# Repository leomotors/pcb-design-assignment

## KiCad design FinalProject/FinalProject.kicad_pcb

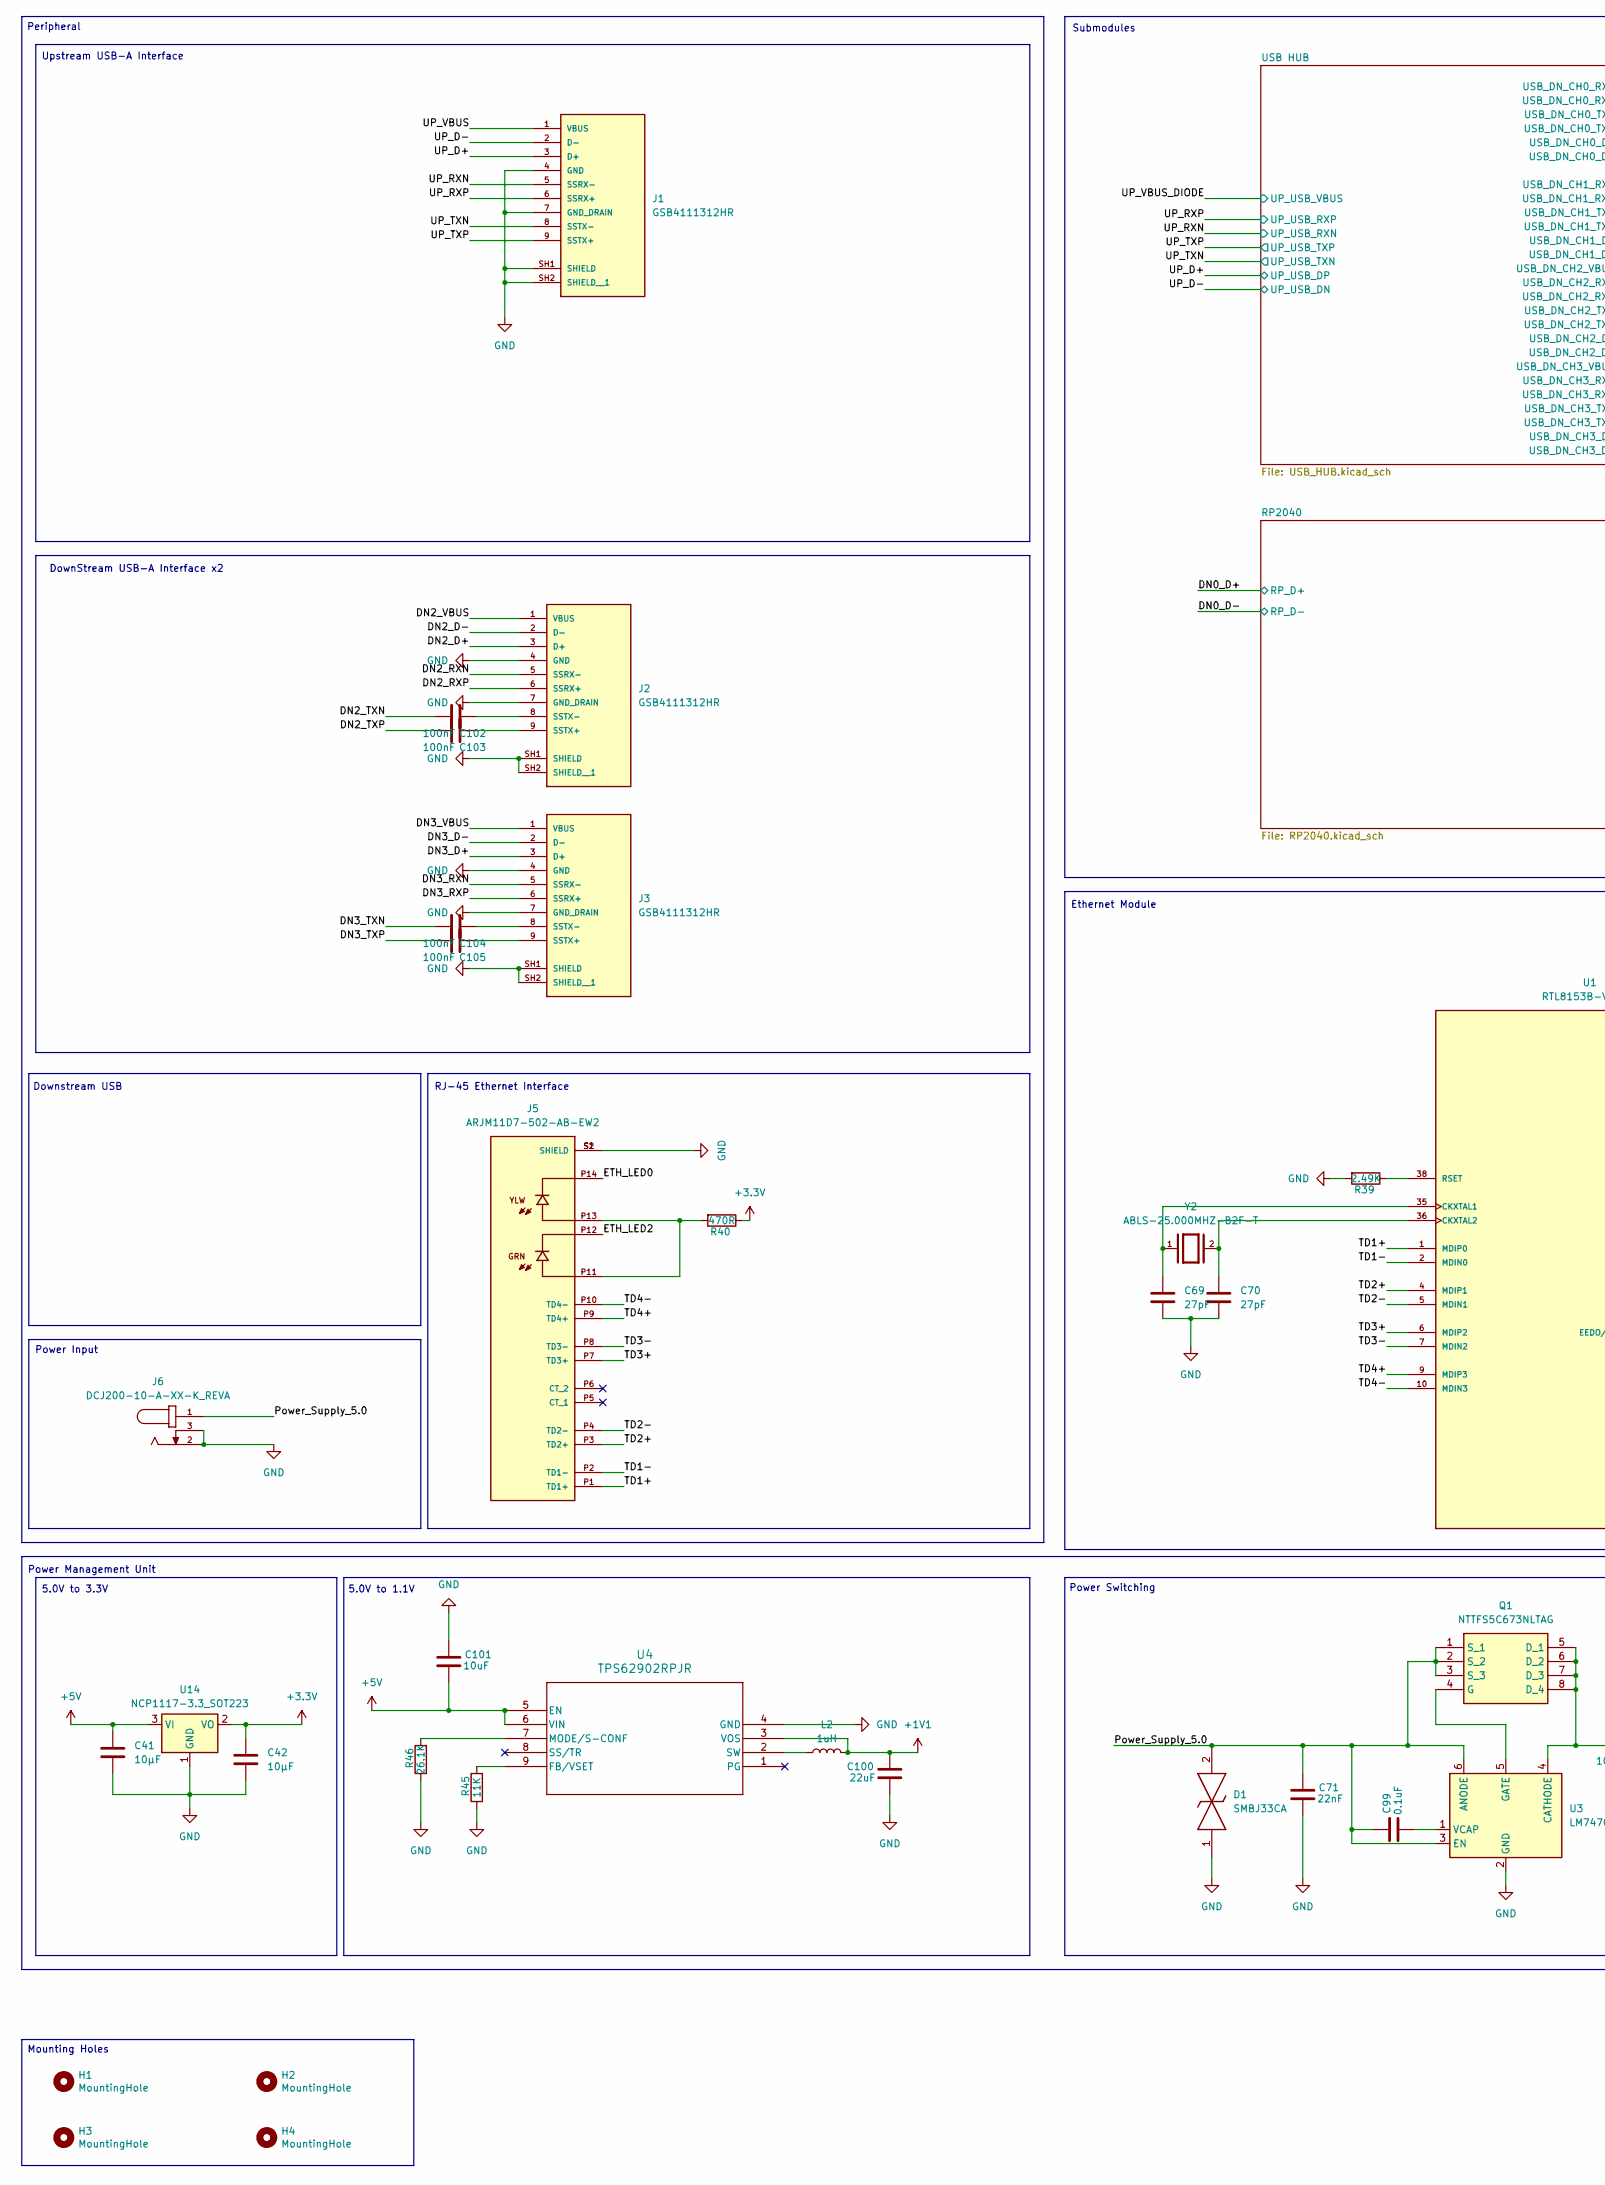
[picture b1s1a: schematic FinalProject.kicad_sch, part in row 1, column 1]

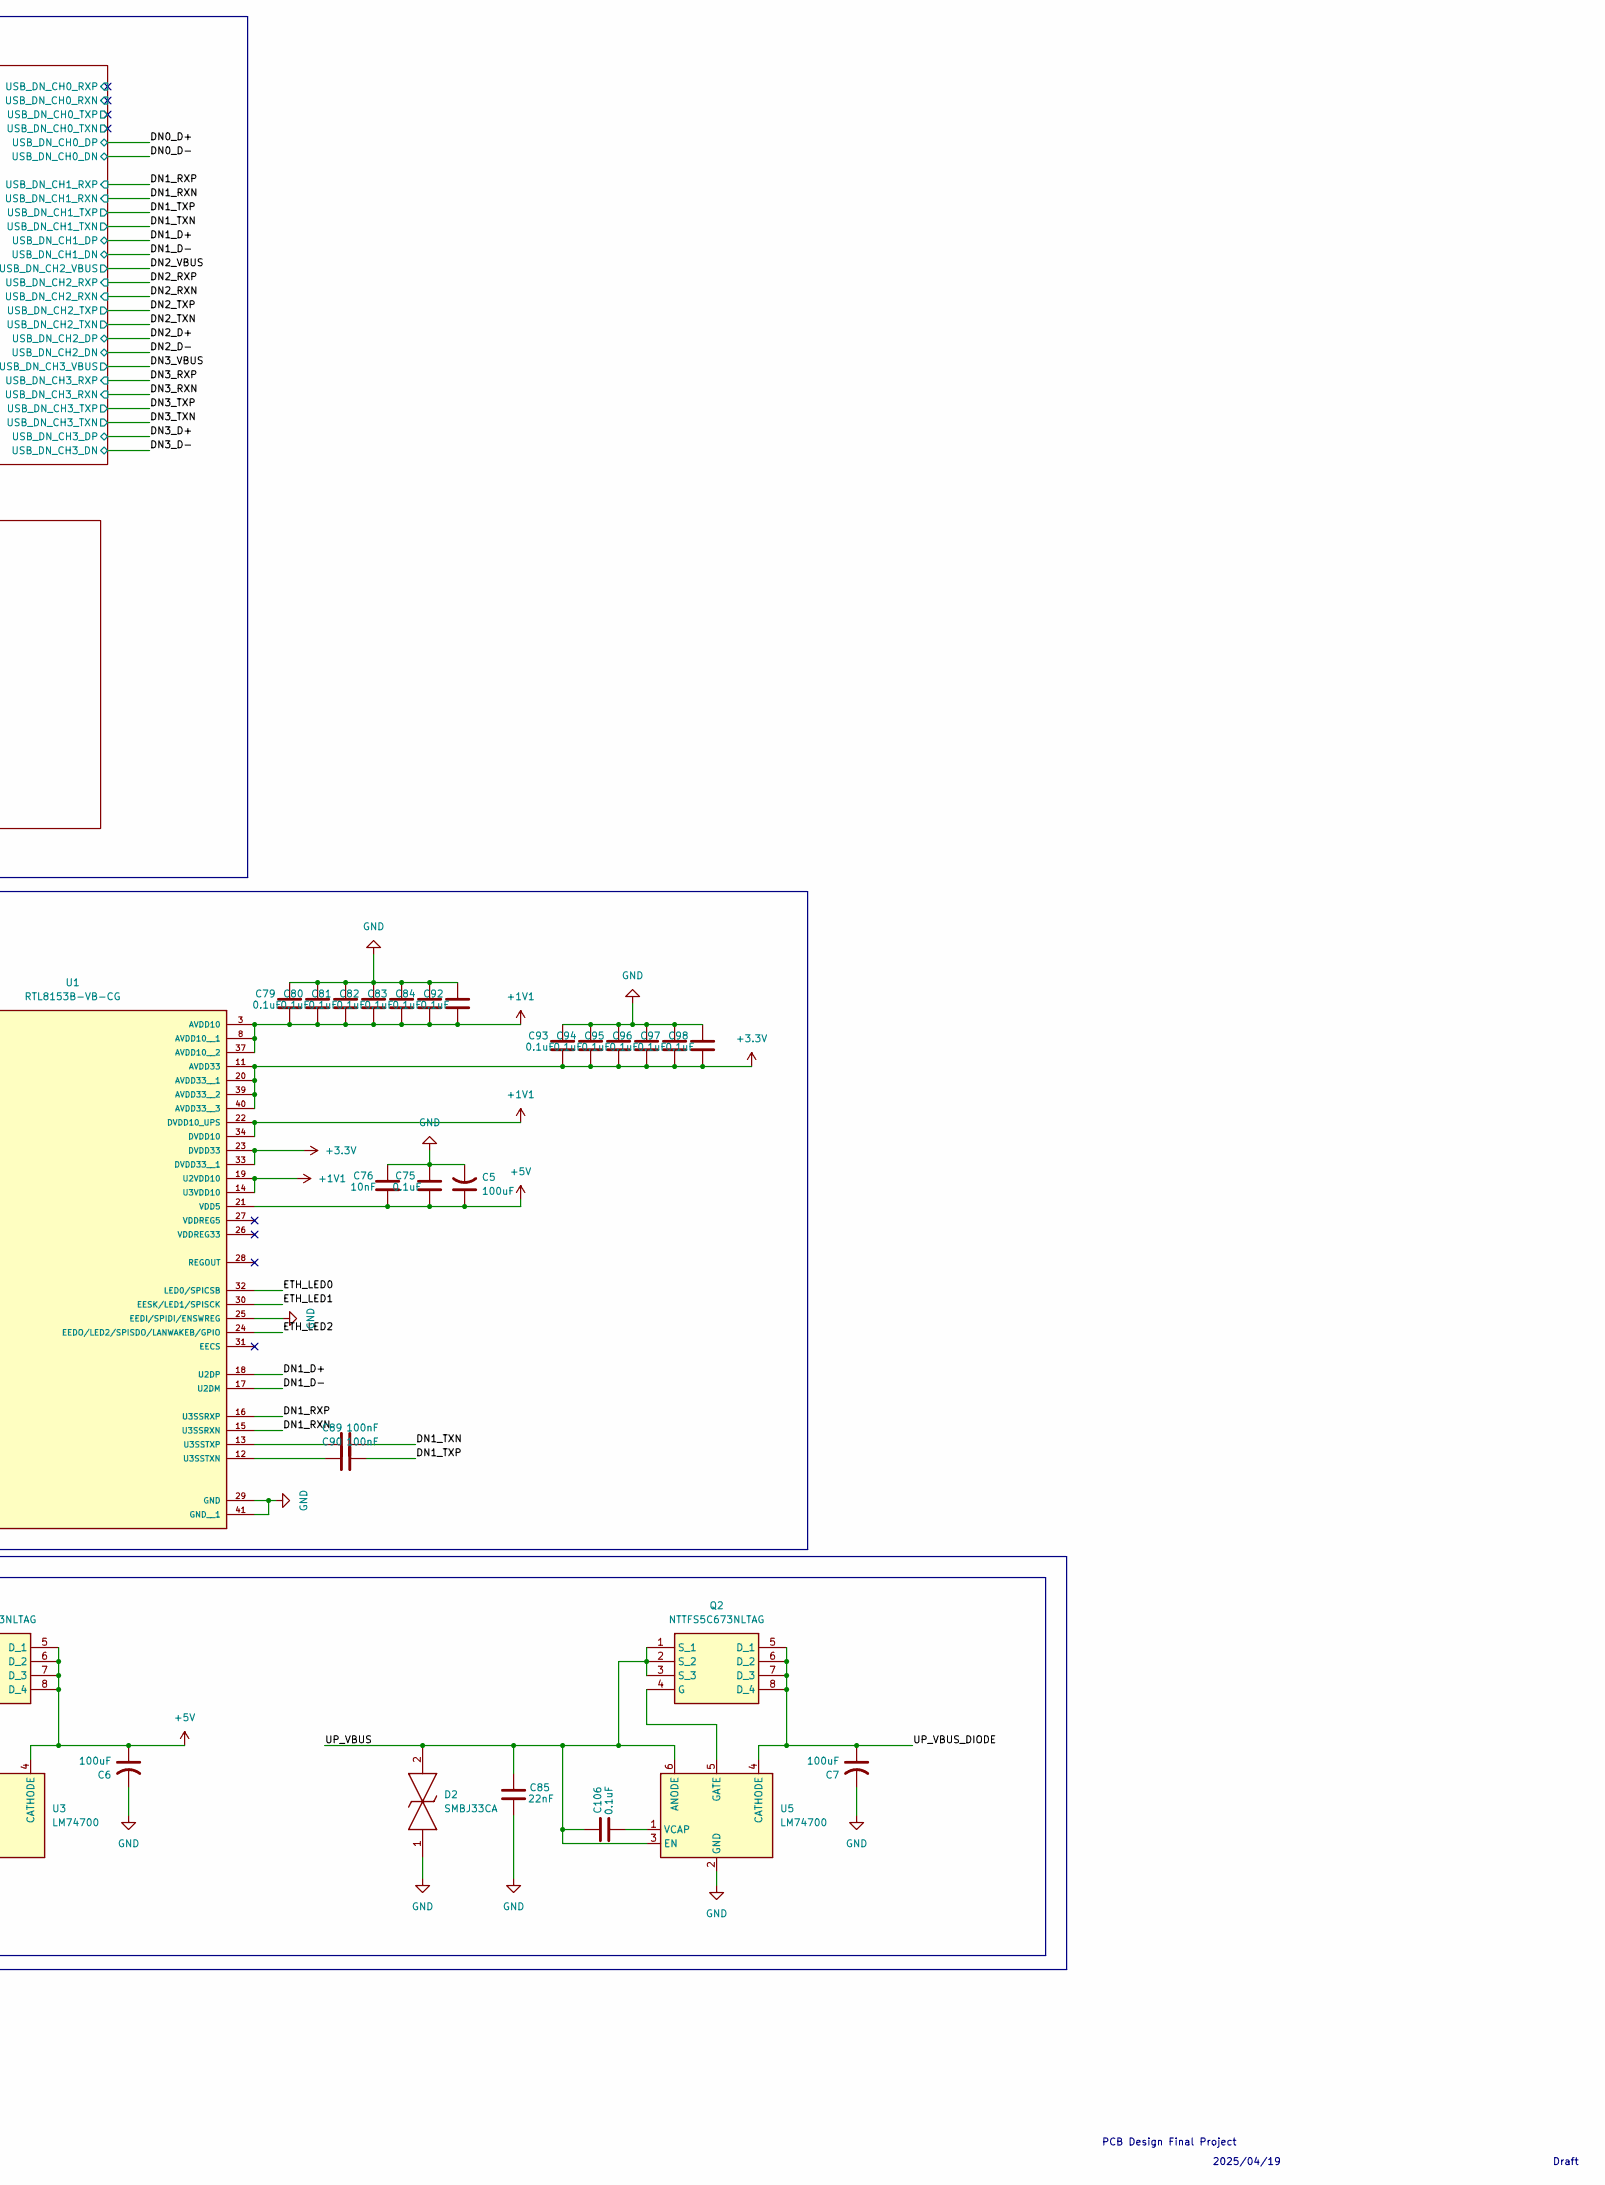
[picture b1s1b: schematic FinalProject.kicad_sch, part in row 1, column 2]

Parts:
C5, C6, C7: 100uF; C_1206_3216Metric
C41, C42: 10μF; C_0603_1608Metric
C69, C70: 27pF; C_0603_1608Metric
C71, C85: 22nF; C_0603_1608Metric
C75, C79, C80, C81, C82, C83, C84, C92, C93, C94, C95, C96, C97, C98, C99, C106: 0.1uF; C_0603_1608Metric
C76: 10nF; C_0603_1608Metric
C89, C90, C102, C103, C104, C105: 100nF; C_0603_1608Metric
C100: 22uF; C_0603_1608Metric
C101: 10uF; C_0603_1608Metric
D1, D2: SMBJ33CA; DIONM5436X261N; Mouser Part Number 576-SMBJ33CA
H1, H2, H3, H4: MountingHole; MountingHole_2.7mm_M2.5
J1, J2, J3: GSB4111312HR; AMPHENOL_GSB4111312HR; PARTREV B
J5: ARJM11D7-502-AB-EW2; ABRACON_ARJM11D7-502-AB-EW2; PARTREV 01-21-20
J6: DCJ200-10-A-XX-K_REVA; GCT_DCJ200-10-A-XX-K_REVA; PARTREV A
L2: 1uH; L_1008_2520Metric
Q1, Q2: NTTFS5C673NLTAG; NVTFS6H854NTAG; Mouser Part Number 863-NTTFS5C673NLTAG
R39: 2.49K; R_0603_1608Metric
R40: 470R; R_0603_1608Metric
R45: 11K; R_0603_1608Metric
R46: 26.1K; R_0603_1608Metric
U1: RTL8153B-VB-CG; QFN40P500X500X90-41N; PARTREV 1.4
U3, U5: LM74700; SOT-23-6
U4: TPS62902RPJR; QFN_902RPJR_TEX
U14: NCP1117-3.3_SOT223; SOT-223-3_TabPin2
Y2: ABLS-25.000MHZ-B2F-T; XTAL_ABLS-25.000MHZ-B2F-T; PARTREV 02.16.2021

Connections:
+1V1: C79.2, C80.2, C81.2, C82.2, C83.2, C84.2, C92.2, C100.1, L2.2, U1.3 (AVDD10), U1.8 (AVDD10__1), U1.14 (U3VDD10), U1.19 (U2VDD10), U1.22 (DVDD10_UPS), U1.34 (DVDD10), U1.37 (AVDD10__2), U4.3 (VOS); also elsewhere on the board
+3.3V: C42.1, C93.2, C94.2, C95.2, C96.2, C97.2, C98.2, R40.1, U1.11 (AVDD33), U1.20 (AVDD33__1), U1.23 (DVDD33), U1.33 (DVDD33__1), U1.39 (AVDD33__2), U1.40 (AVDD33__3), U14.2 (VO); also elsewhere on the board
+5V: C5.1, C6.1, C41.1, C75.2, C76.2, C101.2, Q1.5 (D_1), Q1.6 (D_2), Q1.7 (D_3), Q1.8 (D_4), U1.21 (VDD5), U3.4 (CATHODE), U4.5 (EN), U4.6 (VIN), U14.3 (VI); also elsewhere on the board
/DN1_D+: U1.18 (U2DP); also elsewhere on the board
/DN1_D-: U1.17 (U2DM); also elsewhere on the board
/DN1_RXN: U1.15 (U3SSRXN); also elsewhere on the board
/DN1_RXP: U1.16 (U3SSRXP); also elsewhere on the board
/DN1_TXN: C89.2; also elsewhere on the board
/DN1_TXP: C90.2; also elsewhere on the board
/DN2_D+: J2.3 (D+); also elsewhere on the board
/DN2_D-: J2.2 (D-); also elsewhere on the board
/DN2_RXN: J2.5 (SSRX-); also elsewhere on the board
/DN2_RXP: J2.6 (SSRX+); also elsewhere on the board
/DN2_TXN: C102.2; also elsewhere on the board
/DN2_TXP: C103.2; also elsewhere on the board
/DN2_VBUS: J2.1 (VBUS); also elsewhere on the board
/DN3_D+: J3.3 (D+); also elsewhere on the board
/DN3_D-: J3.2 (D-); also elsewhere on the board
/DN3_RXN: J3.5 (SSRX-); also elsewhere on the board
/DN3_RXP: J3.6 (SSRX+); also elsewhere on the board
/DN3_TXN: C104.2; also elsewhere on the board
/DN3_TXP: C105.2; also elsewhere on the board
/DN3_VBUS: J3.1 (VBUS); also elsewhere on the board
/ETH_LED0: J5.P14, U1.32 (LED0/SPICSB)
/ETH_LED1: U1.30 (EESK/LED1/SPISCK)
/ETH_LED2: J5.P12, U1.24 (EEDO/LED2/SPISDO/LANWAKEB/GPIO)
/Power_Supply_5.0: C71.1, C99.1, D1.2, J6.1, Q1.1 (S_1), Q1.2 (S_2), Q1.3 (S_3), U3.3 (EN), U3.6 (ANODE)
/TD1+: J5.P1 (TD1+), U1.1 (MDIP0)
/TD1-: J5.P2 (TD1-), U1.2 (MDIN0)
/TD2+: J5.P3 (TD2+), U1.4 (MDIP1)
/TD2-: J5.P4 (TD2-), U1.5 (MDIN1)
/TD3+: J5.P7 (TD3+), U1.6 (MDIP2)
/TD3-: J5.P8 (TD3-), U1.7 (MDIN2)
/TD4+: J5.P9 (TD4+), U1.9 (MDIP3)
/TD4-: J5.P10 (TD4-), U1.10 (MDIN3)
/UP_D+: J1.3 (D+); also elsewhere on the board
/UP_D-: J1.2 (D-); also elsewhere on the board
/UP_RXN: J1.5 (SSRX-); also elsewhere on the board
/UP_RXP: J1.6 (SSRX+); also elsewhere on the board
/UP_TXN: J1.8 (SSTX-); also elsewhere on the board
/UP_TXP: J1.9 (SSTX+); also elsewhere on the board
/UP_VBUS: C85.1, C106.1, D2.2, J1.1 (VBUS), Q2.1 (S_1), Q2.2 (S_2), Q2.3 (S_3), U5.3 (EN), U5.6 (ANODE)
/UP_VBUS_DIODE: C7.1, Q2.5 (D_1), Q2.6 (D_2), Q2.7 (D_3), Q2.8 (D_4), U5.4 (CATHODE); also elsewhere on the board
GND: C5.2, C6.2, C7.2, C41.2, C42.2, C69.2, C70.2, C71.2, C75.1, C76.1, C79.1, C80.1, C81.1, C82.1, C83.1, C84.1, C85.2, C92.1, C93.1, C94.1, C95.1, C96.1, C97.1, C98.1, C100.2, C101.1, D1.1, D2.1, J1.4 (GND), J1.7 (GND_DRAIN), J1.SH1 (SHIELD), J1.SH2 (SHIELD__1), J2.4 (GND), J2.7 (GND_DRAIN), J2.SH1 (SHIELD), J2.SH2 (SHIELD__1), J3.4 (GND), J3.7 (GND_DRAIN), J3.SH1 (SHIELD), J3.SH2 (SHIELD__1), J5.S1 (SHIELD), J5.S2 (SHIELD), J6.2, J6.3, R39.2, R45.1, R46.1, U1.25 (EEDI/SPIDI/ENSWREG), U1.29 (GND), U1.41 (GND__1), U3.2 (GND), U4.4 (GND), U5.2 (GND), U14.1 (GND); also elsewhere on the board
unnamed: C103.1, J2.9 (SSTX+)
unnamed: C102.1, J2.8 (SSTX-)
unnamed: C105.1, J3.9 (SSTX+)
unnamed: C104.1, J3.8 (SSTX-)
unnamed: J5.P11, J5.P13, R40.2
unnamed: Q1.4 (G), U3.5 (GATE)
unnamed: Q2.4 (G), U5.5 (GATE)
unnamed: C69.1, U1.35 (CKXTAL1), Y2.1
unnamed: C70.1, U1.36 (CKXTAL2), Y2.2
unnamed: R39.1, U1.38 (RSET)
unnamed: C90.1, U1.12 (U3SSTXN)
unnamed: C89.1, U1.13 (U3SSTXP)
unnamed: C99.2, U3.1 (VCAP)
unnamed: R45.2, U4.9 (FB/VSET)
unnamed: R46.2, U4.7 (MODE/S-CONF)
unnamed: L2.1, U4.2 (SW)
unnamed: C106.2, U5.1 (VCAP)

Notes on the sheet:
Downstream USB
2025/04/19
RJ-45 Ethernet Interface
Draft
PCB Design Final Project
5.0V to 1.1V
Ethernet Module
DownStream USB-A Interface x2
5.0V to 3.3V
Upstream USB-A Interface
Submodules
Power Switching
Power Management Unit
Peripheral
Power Input
Mounting Holes

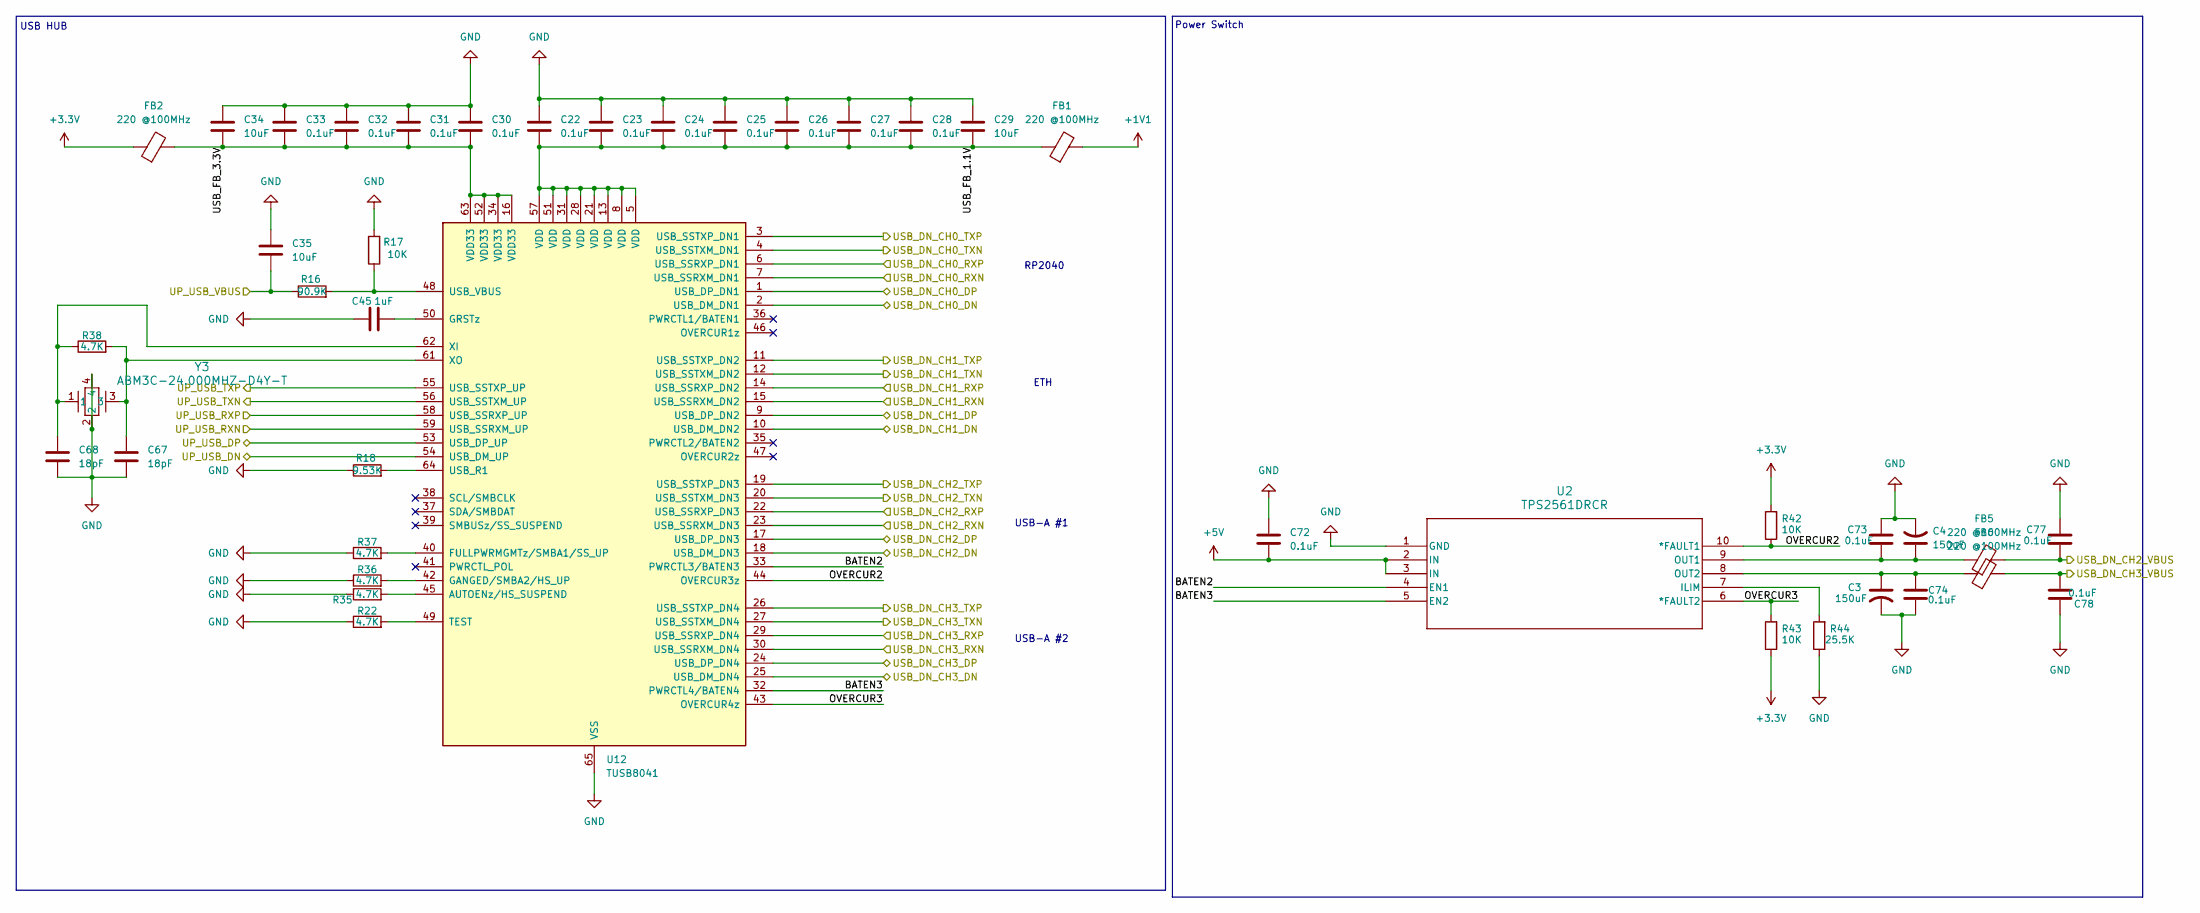
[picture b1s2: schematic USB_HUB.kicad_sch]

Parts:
C3, C4: 150uF; C_1210_3225Metric
C22, C23, C24, C25, C26, C27, C28, C30, C31, C32, C33, C72, C73, C74, C77, C78: 0.1uF; C_0603_1608Metric
C29, C34, C35: 10uF; C_0603_1608Metric
C45: 1uF; C_0603_1608Metric
C67, C68: 18pF; C_0603_1608Metric
FB1, FB2, FB5, FB6: 220 @100MHz; L_0805_2012Metric
R16: 90.9K; R_0402_1005Metric
R17, R42, R43: 10K; R_0402_1005Metric
R18: 9.53K; R_0402_1005Metric
R22, R38: 4.7K; R_0603_1608Metric
R35, R36, R37: 4.7K; R_0402_1005Metric
R44: 25.5K; R_0402_1005Metric
U2: TPS2561DRCR; DRC10_2P4X1P65
U12: TUSB8041; QFN-64-1EP_9x9mm_P0.5mm_EP6x6mm_ThermalVias
Y3: ABM3C-24.000MHZ-D4Y-T; CRYSTAL_ABM3C_ABR

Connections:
+1V1: FB1.2; also elsewhere on the board
+3.3V: FB2.1, R42.2, R43.1; also elsewhere on the board
+5V: C72.2, U2.2 (IN), U2.3 (IN); also elsewhere on the board
/DN0_D+: U12.1 (USB_DP_DN1); also elsewhere on the board
/DN0_D-: U12.2 (USB_DM_DN1); also elsewhere on the board
/DN1_D+: U12.9 (USB_DP_DN2); also elsewhere on the board
/DN1_D-: U12.10 (USB_DM_DN2); also elsewhere on the board
/DN1_RXN: U12.15 (USB_SSRXM_DN2); also elsewhere on the board
/DN1_RXP: U12.14 (USB_SSRXP_DN2); also elsewhere on the board
/DN1_TXN: U12.12 (USB_SSTXM_DN2); also elsewhere on the board
/DN1_TXP: U12.11 (USB_SSTXP_DN2); also elsewhere on the board
/DN2_D+: U12.17 (USB_DP_DN3); also elsewhere on the board
/DN2_D-: U12.18 (USB_DM_DN3); also elsewhere on the board
/DN2_RXN: U12.23 (USB_SSRXM_DN3); also elsewhere on the board
/DN2_RXP: U12.22 (USB_SSRXP_DN3); also elsewhere on the board
/DN2_TXN: U12.20 (USB_SSTXM_DN3); also elsewhere on the board
/DN2_TXP: U12.19 (USB_SSTXP_DN3); also elsewhere on the board
/DN2_VBUS: C77.2, FB5.2; also elsewhere on the board
/DN3_D+: U12.24 (USB_DP_DN4); also elsewhere on the board
/DN3_D-: U12.25 (USB_DM_DN4); also elsewhere on the board
/DN3_RXN: U12.30 (USB_SSRXM_DN4); also elsewhere on the board
/DN3_RXP: U12.29 (USB_SSRXP_DN4); also elsewhere on the board
/DN3_TXN: U12.27 (USB_SSTXM_DN4); also elsewhere on the board
/DN3_TXP: U12.26 (USB_SSTXP_DN4); also elsewhere on the board
/DN3_VBUS: C78.2, FB6.2; also elsewhere on the board
/UP_D+: U12.53 (USB_DP_UP); also elsewhere on the board
/UP_D-: U12.54 (USB_DM_UP); also elsewhere on the board
/UP_RXN: U12.59 (USB_SSRXM_UP); also elsewhere on the board
/UP_RXP: U12.58 (USB_SSRXP_UP); also elsewhere on the board
/UP_TXN: U12.56 (USB_SSTXM_UP); also elsewhere on the board
/UP_TXP: U12.55 (USB_SSTXP_UP); also elsewhere on the board
/UP_VBUS_DIODE: C35.2, R16.1; also elsewhere on the board
/USB HUB/BATEN2: U2.4 (EN1), U12.33 (PWRCTL3/BATEN3)
/USB HUB/BATEN3: U2.5 (EN2), U12.32 (PWRCTL4/BATEN4)
/USB HUB/OVERCUR2: R42.1, U2.10 (*FAULT1), U12.44 (OVERCUR3z)
/USB HUB/OVERCUR3: R43.2, U2.6 (*FAULT2), U12.43 (OVERCUR4z)
/USB HUB/USB_DN_CH0_RXN: U12.7 (USB_SSRXM_DN1)
/USB HUB/USB_DN_CH0_RXP: U12.6 (USB_SSRXP_DN1)
/USB HUB/USB_DN_CH0_TXN: U12.4 (USB_SSTXM_DN1)
/USB HUB/USB_DN_CH0_TXP: U12.3 (USB_SSTXP_DN1)
/USB HUB/USB_FB_1.1V: C22.2, C23.2, C24.2, C25.2, C26.2, C27.2, C28.2, C29.2, FB1.1, U12.5 (VDD), U12.8 (VDD), U12.13 (VDD), U12.21 (VDD), U12.28 (VDD), U12.31 (VDD), U12.51 (VDD), U12.57 (VDD)
/USB HUB/USB_FB_3.3V: C30.2, C31.2, C32.2, C33.2, C34.2, FB2.2, U12.16 (VDD33), U12.34 (VDD33), U12.52 (VDD33), U12.63 (VDD33)
GND: C3.2, C4.2, C22.1, C23.1, C24.1, C25.1, C26.1, C27.1, C28.1, C29.1, C30.1, C31.1, C32.1, C33.1, C34.1, C35.1, C45.1, C67.2, C68.2, C72.1, C73.1, C74.1, C77.1, C78.1, R17.2, R18.1, R22.1, R35.1, R36.1, R37.1, R44.1, U2.1 (GND), U12.65 (VSS), Y3.2, Y3.4; also elsewhere on the board
unnamed: R44.2, U2.7 (ILIM)
unnamed: C4.1, C73.2, FB5.1, U2.9 (OUT1)
unnamed: C3.1, C74.2, FB6.1, U2.8 (OUT2)
unnamed: R35.2, U12.45 (AUTOENz/HS_SUSPEND)
unnamed: R37.2, U12.40 (FULLPWRMGMTz/SMBA1/SS_UP)
unnamed: R36.2, U12.42 (GANGED/SMBA2/HS_UP)
unnamed: C45.2, U12.50 (GRSTz)
unnamed: R22.2, U12.49 (TEST)
unnamed: R18.2, U12.64 (USB_R1)
unnamed: R16.2, R17.1, U12.48 (USB_VBUS)
unnamed: C68.1, R38.1, U12.62 (XI), Y3.1
unnamed: C67.1, R38.2, U12.61 (XO), Y3.3

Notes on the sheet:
USB HUB
USB-A #1
RP2040
USB-A #2
ETH
Power Switch

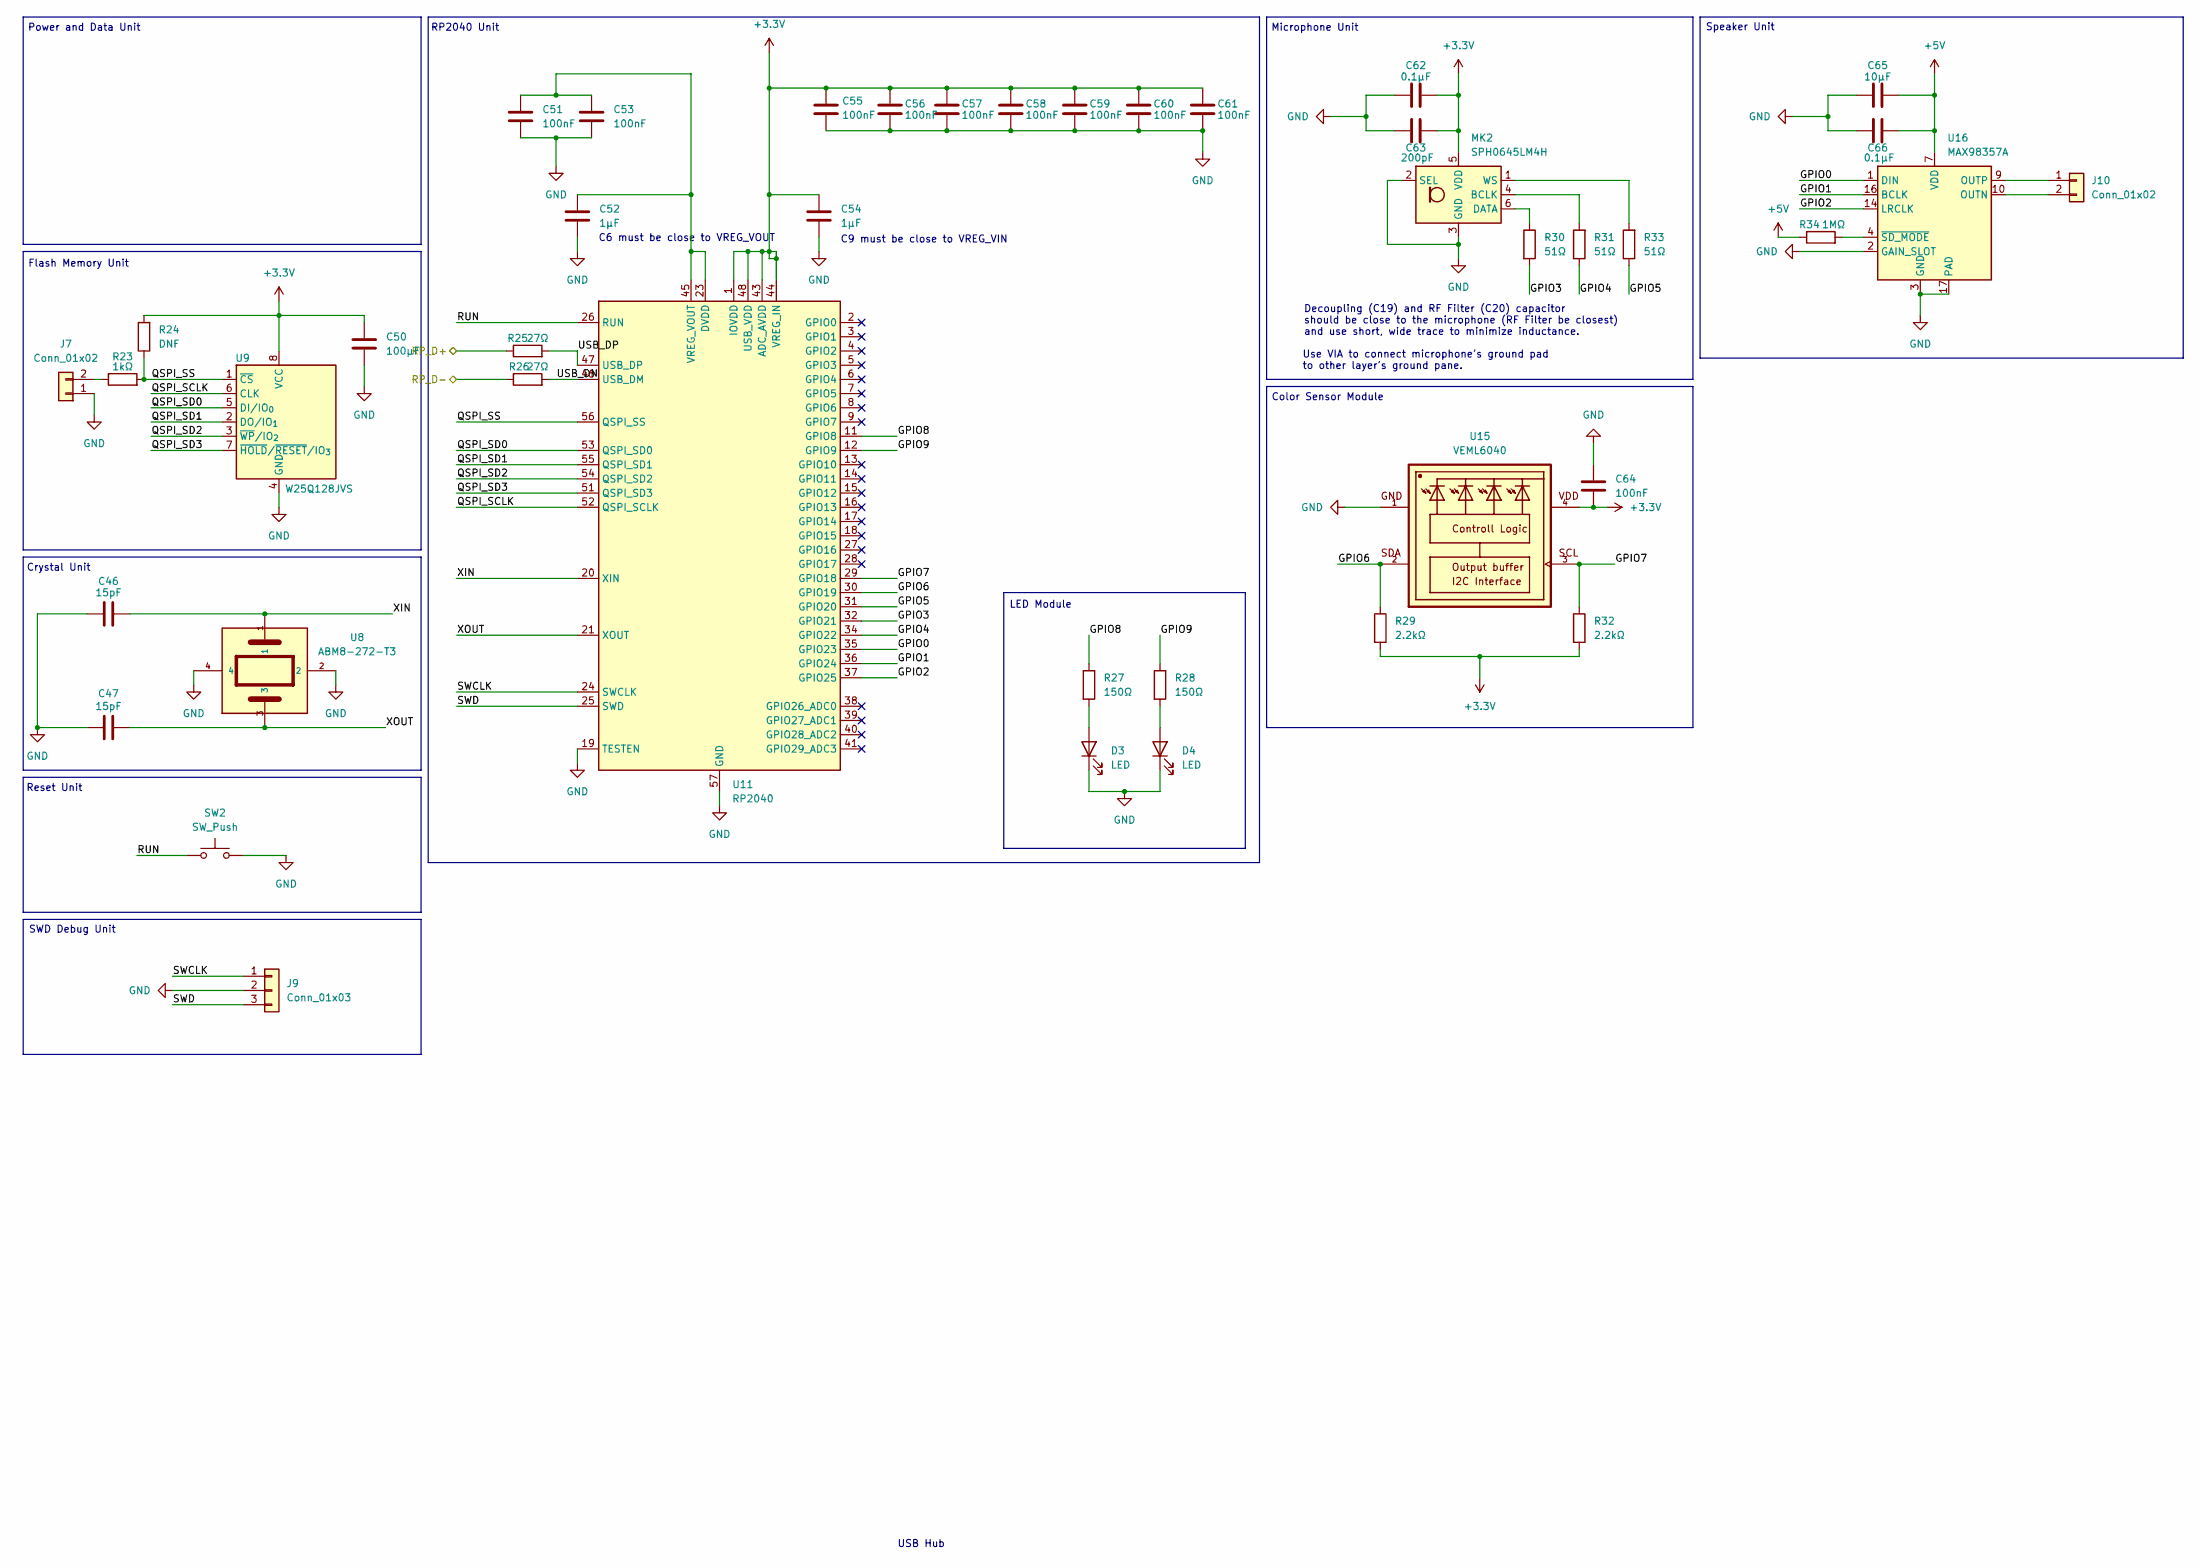
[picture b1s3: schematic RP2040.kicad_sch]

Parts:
C46, C47: 15pF; C_0402_1005Metric
C50: 100μF; C_1206_3216Metric
C51, C53, C55, C56, C57, C58, C59, C60, C61, C64: 100nF; C_0603_1608Metric
C52, C54: 1μF; C_0402_1005Metric
C62, C66: 0.1μF; C_0603_1608Metric
C63: 200pF; C_0603_1608Metric
C65: 10μF; C_0603_1608Metric
D3, D4: LED; LED_0603_1608Metric
J7, J10: Conn_01x02; PinSocket_1x02_P2.54mm_Vertical
J9: Conn_01x03; PinSocket_1x03_P2.54mm_Vertical
MK2: SPH0645LM4H; Knowles_SPH0645LM4H-6_3.5x2.65mm
R23: 1kΩ; R_0603_1608Metric
R24: DNF; R_0603_1608Metric
R25, R26: 27Ω; R_0603_1608Metric
R27, R28: 150Ω; R_0603_1608Metric
R29, R32: 2.2kΩ; R_0603_1608Metric
R30, R31, R33: 51Ω; R_0603_1608Metric
R34: 1MΩ; R_0603_1608Metric
SW2: SW_Push; SW_PUSH_1P1T_6x3.5mm_H4.3_APEM_MJTP1243
U8: ABM8-272-T3
U9: W25Q128JVS; SOIC-8_5.3x5.3mm_P1.27mm
U11: RP2040; QFN-56-1EP_7x7mm_P0.4mm_EP3.2x3.2mm
U15: VEML6040; VISHAY_VEML6040_1.25X2X1
U16: MAX98357A; TQFN-16-1EP_3x3mm_P0.5mm_EP1.23x1.23mm

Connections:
+3.3V: C50.1, C54.1, C55.1, C56.1, C57.1, C58.1, C59.1, C60.1, C61.1, C62.2, C63.2, C64.2, MK2.5 (VDD), R24.2, R29.2, R32.2, U9.8 (VCC), U11.1 (IOVDD), U11.10 (IOVDD), U11.22 (IOVDD), U11.33 (IOVDD), U11.42 (IOVDD), U11.43 (ADC_AVDD), U11.44 (VREG_IN), U11.48 (USB_VDD), U11.49 (IOVDD), U15.4; also elsewhere on the board
+5V: C65.2, C66.2, R34.1, U16.7 (VDD), U16.8 (VDD); also elsewhere on the board
/DN0_D+: R25.1; also elsewhere on the board
/DN0_D-: R26.1; also elsewhere on the board
/RP2040/GPIO0: U11.35 (GPIO23), U16.1 (DIN)
/RP2040/GPIO1: U11.36 (GPIO24), U16.16 (BCLK)
/RP2040/GPIO2: U11.37 (GPIO25), U16.14 (LRCLK)
/RP2040/GPIO3: R30.2, U11.32 (GPIO21)
/RP2040/GPIO4: R31.1, U11.34 (GPIO22)
/RP2040/GPIO5: R33.1, U11.31 (GPIO20)
/RP2040/GPIO6: R29.1, U11.30 (GPIO19), U15.2
/RP2040/GPIO7: R32.1, U11.29 (GPIO18), U15.3
/RP2040/GPIO8: R27.1, U11.11 (GPIO8)
/RP2040/GPIO9: R28.1, U11.12 (GPIO9)
/RP2040/QSPI_SCLK: U9.6 (CLK), U11.52 (QSPI_SCLK)
/RP2040/QSPI_SD0: U9.5 (DI/IO_{0}), U11.53 (QSPI_SD0)
/RP2040/QSPI_SD1: U9.2 (DO/IO_{1}), U11.55 (QSPI_SD1)
/RP2040/QSPI_SD2: U9.3 (~WP/IO_{2}), U11.54 (QSPI_SD2)
/RP2040/QSPI_SD3: U9.7 (~HOLD/~RESET/IO_{3}), U11.51 (QSPI_SD3)
/RP2040/QSPI_SS: R23.2, R24.1, U9.1 (~CS), U11.56 (QSPI_SS)
/RP2040/RUN: SW2.1, U11.26 (RUN)
/RP2040/SWCLK: J9.1, U11.24 (SWCLK)
/RP2040/SWD: J9.3, U11.25 (SWD)
/RP2040/USB_DN: R26.2, U11.46 (USB_DM)
/RP2040/USB_DP: R25.2, U11.47 (USB_DP)
/RP2040/XIN: C46.2, U8.1, U11.20 (XIN)
/RP2040/XOUT: C47.2, U8.3, U11.21 (XOUT)
GND: C46.1, C47.1, C50.2, C51.2, C52.2, C53.2, C54.2, C55.2, C56.2, C57.2, C58.2, C59.2, C60.2, C61.2, C62.1, C63.1, C64.1, C65.1, C66.1, D3.1 (K), D4.1 (K), J7.1, J9.2, MK2.2 (SEL), MK2.3 (GND), SW2.2, U8.2, U8.4, U9.4 (GND), U11.19 (TESTEN), U11.57 (GND), U15.1, U16.2 (GAIN_SLOT), U16.3 (GND), U16.11 (GND), U16.15 (GND), U16.17 (PAD); also elsewhere on the board
unnamed: D3.2 (A), R27.2
unnamed: D4.2 (A), R28.2
unnamed: J7.2, R23.1
unnamed: J10.1, U16.9 (OUTP)
unnamed: J10.2, U16.10 (OUTN)
unnamed: MK2.4 (BCLK), R31.2
unnamed: MK2.6 (DATA), R30.1
unnamed: MK2.1 (WS), R33.2
unnamed: C51.1, C52.1, C53.1, U11.23 (DVDD), U11.45 (VREG_VOUT), U11.50 (DVDD)
unnamed: R34.2, U16.4 (~SD_MODE)

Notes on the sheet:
Microphone Unit
Reset Unit
Color Sensor Module
LED Module
RP2040 Unit
USB Hub
Flash Memory Unit
Power and Data Unit
C9 must be close to VREG_VIN
C6 must be close to VREG_VOUT
Decoupling (C19) and RF Filter (C20) capacitor should be close to the microphone (RF Filter be closest) and use short, wide trace to minimize inductance.
Crystal Unit
Use VIA to connect microphone's ground pad to other layer's ground pane.
SWD Debug Unit
Speaker Unit
